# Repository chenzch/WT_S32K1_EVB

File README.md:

MiniEVB for S32K1. Powered by WTMEC.

<Peter_Chen@wtmec.com>

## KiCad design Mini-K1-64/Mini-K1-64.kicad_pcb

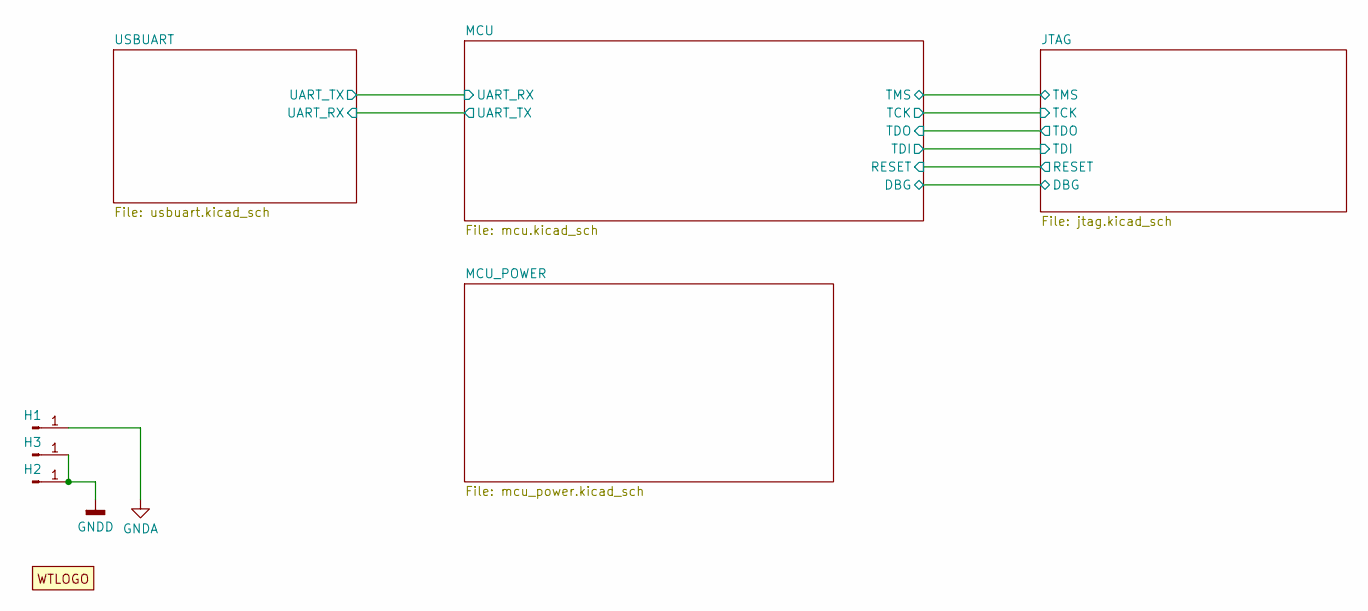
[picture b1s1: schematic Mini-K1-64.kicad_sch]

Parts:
H1, H2, H3: Conn_01x01_Pin; MountingHole_2.2mm_M2_ISO7380_Pad
LOGO1: WTLogo

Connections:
GNDA: H1.1; also elsewhere on the board
GNDD: H2.1, H3.1; also elsewhere on the board

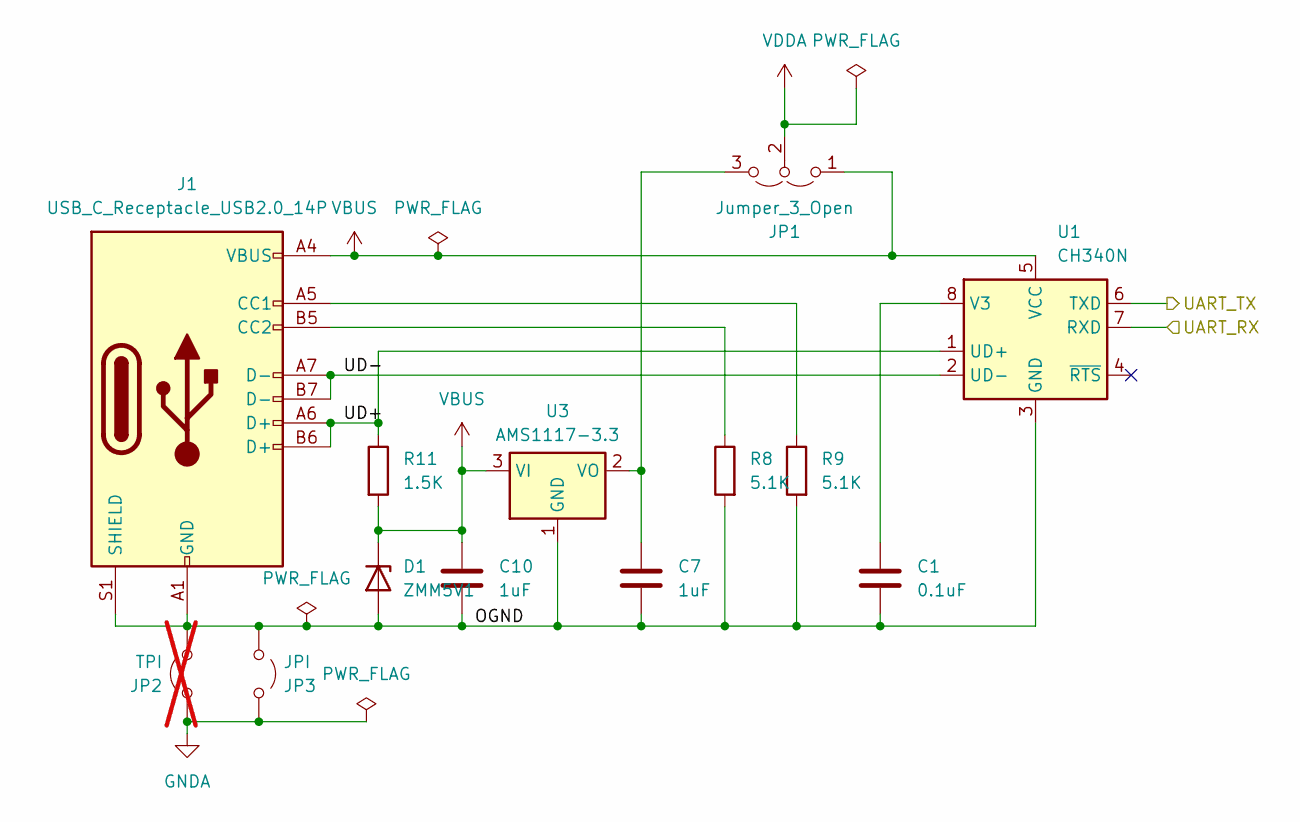
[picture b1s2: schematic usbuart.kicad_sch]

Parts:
C1: 0.1uF; C_0805_2012Metric
C7, C10: 1uF; C_0805_2012Metric
D1: ZMM5V1; D_MiniMELF
J1: USB_C_Receptacle_USB2.0_14P; USB_C_Receptacle_GCT_USB4105-xx-A_16P_TopMnt_Horizontal
JP1: Jumper_3_Open; PinHeader_1x03_P2.54mm_Vertical
JP2: TPI; PinHeader_1x02_P2.54mm_Vertical; not fitted
JP3: JPI; PinHeader_1x02_P2.54mm_Vertical
R8, R9: 5.1K; R_0805_2012Metric
R11: 1.5K; R_0805_2012Metric
U1: CH340N; SOP-8_3.9x4.9mm_P1.27mm
U3: AMS1117-3.3; SOT-223-3_TabPin2

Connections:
/MCU/UART_RX: U1.6 (TXD); also elsewhere on the board
/MCU/UART_TX: U1.7 (RXD); also elsewhere on the board
/USBUART/OGND: C1.2, C7.2, C10.2, D1.2 (A), J1.A1 (GND), J1.A12 (GND), J1.B1 (GND), J1.B12 (GND), J1.S1 (SHIELD), JP2.2 (B), JP3.2 (B), R8.2, R9.2, U1.3 (GND), U3.1 (GND)
/USBUART/UD+: J1.A6 (D+), J1.B6 (D+), R11.1, U1.1 (UD+)
/USBUART/UD-: J1.A7 (D-), J1.B7 (D-), U1.2 (UD-)
GNDA: JP2.1 (A), JP3.1 (A); also elsewhere on the board
unnamed: J1.A5 (CC1), R9.1
unnamed: J1.B5 (CC2), R8.1
unnamed: C7.1, JP1.3 (B), U3.2 (VO)
unnamed: C1.1, U1.8 (V3)
VBUS: C10.1, D1.1 (K), J1.A4 (VBUS), J1.A9 (VBUS), J1.B4 (VBUS), J1.B9 (VBUS), JP1.1 (A), R11.2, U1.5 (VCC), U3.3 (VI)
VDDA: JP1.2 (C); also elsewhere on the board

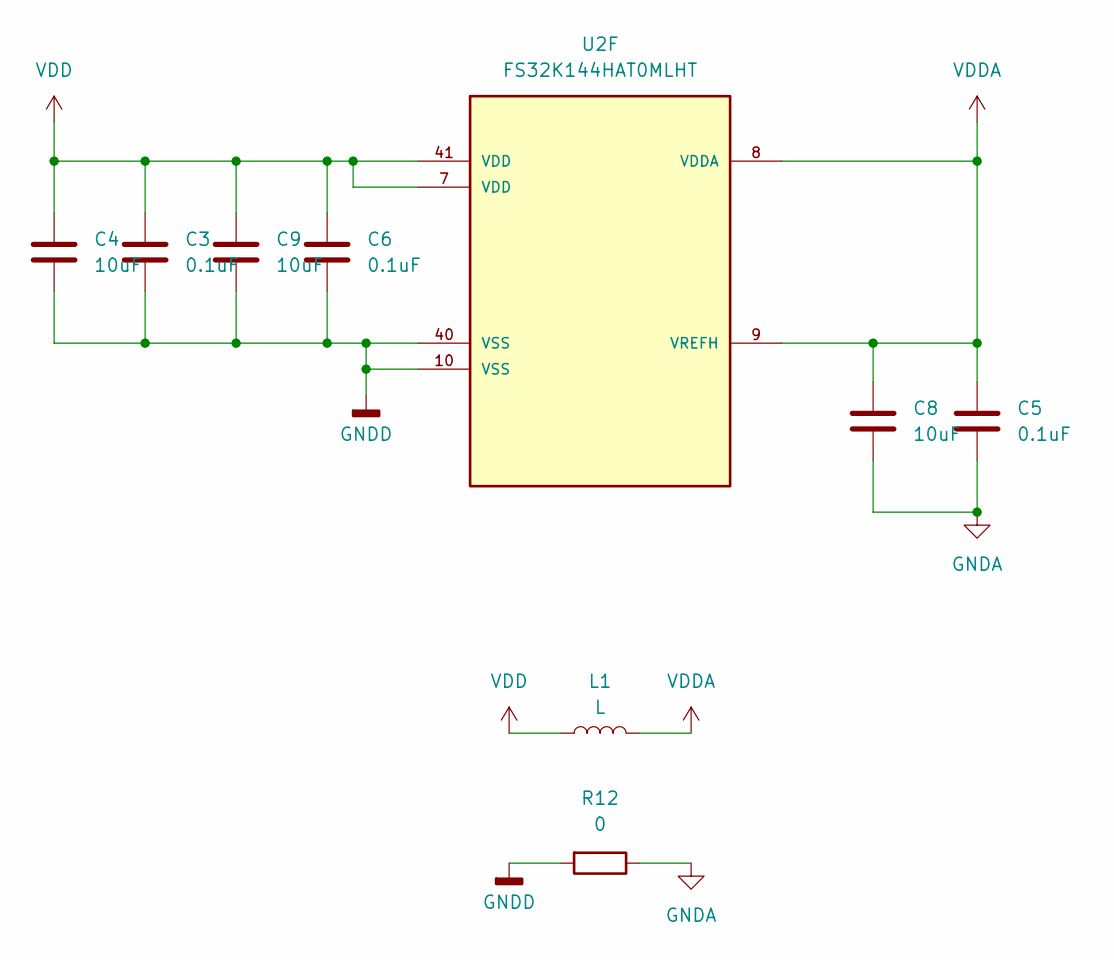
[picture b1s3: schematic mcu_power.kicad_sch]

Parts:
C3, C5, C6: 0.1uF; C_0805_2012Metric
C4, C8, C9: 10uF; C_0805_2012Metric
L1: L; L_0805_2012Metric
R12: 0; R_0805_2012Metric
U2: FS32K144HAT0MLHT; LQFP-64_10x10mm_P0.5mm

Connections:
GNDA: C5.2, C8.2, R12.1; also elsewhere on the board
GNDD: C3.2, C4.2, C6.2, C9.2, R12.2, U2.10 (VSS), U2.40 (VSS); also elsewhere on the board
VDD: C3.1, C4.1, C6.1, C9.1, L1.1, U2.7 (VDD), U2.41 (VDD); also elsewhere on the board
VDDA: C5.1, C8.1, L1.2, U2.8 (VDDA), U2.9 (VREFH); also elsewhere on the board

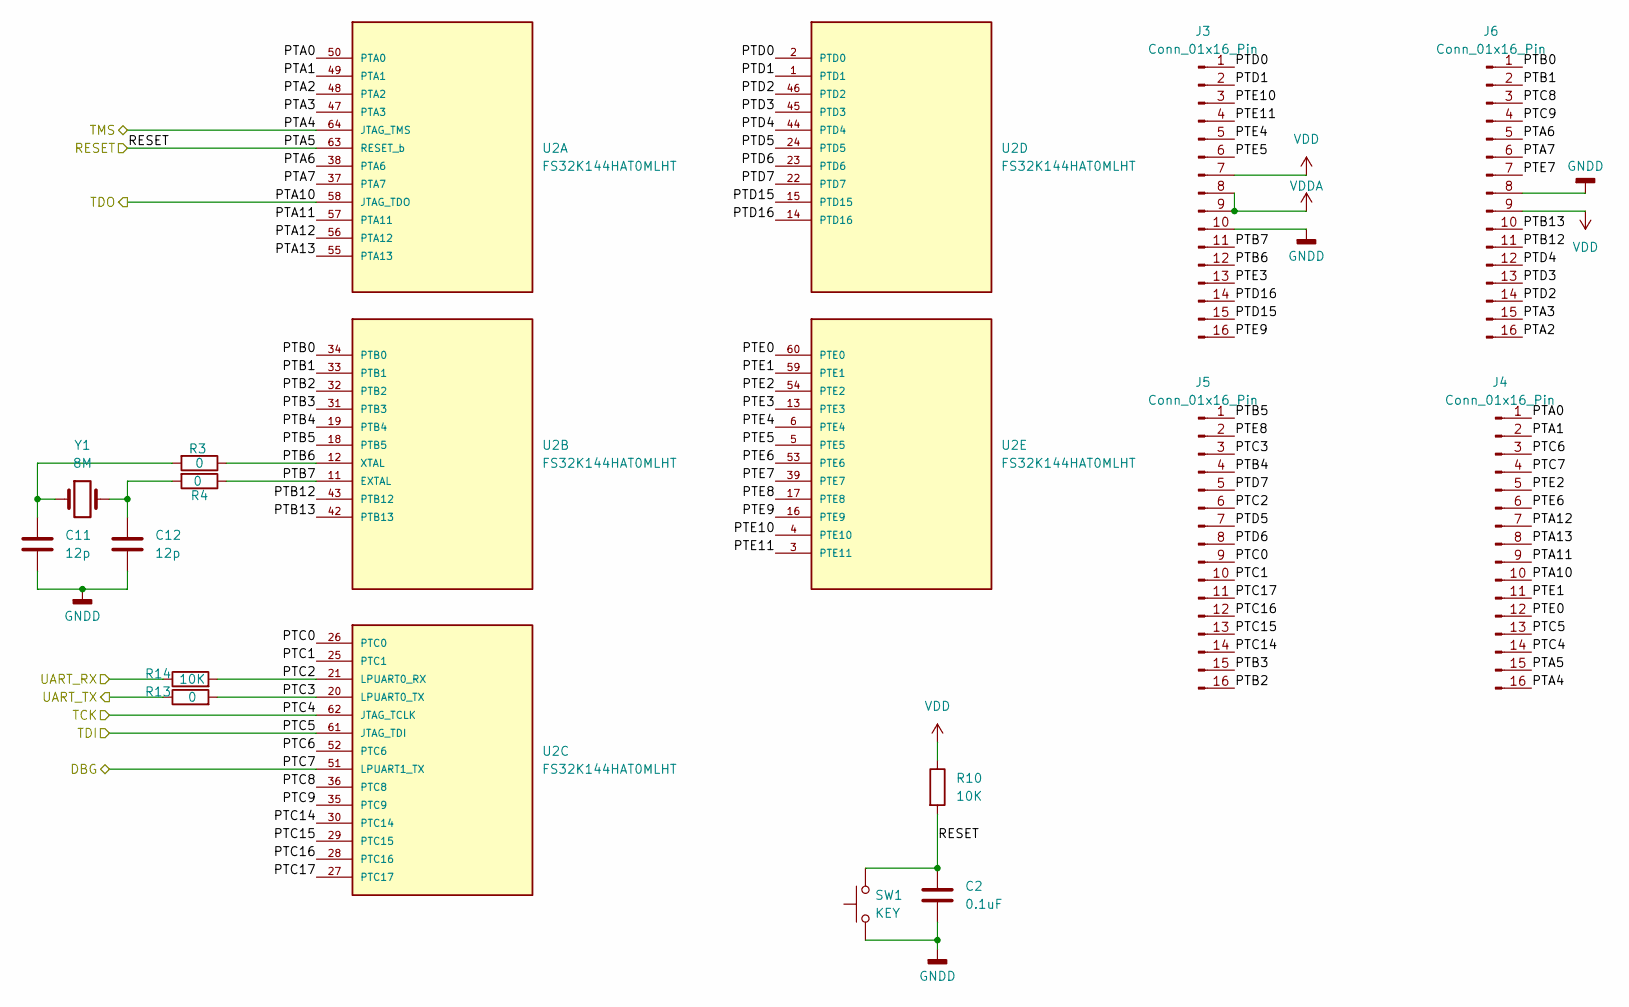
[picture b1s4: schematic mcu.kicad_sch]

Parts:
C2: 0.1uF; C_0805_2012Metric
C11, C12: 12p; C_0805_2012Metric
J3, J4, J5, J6: Conn_01x16_Pin; PinHeader_2x08_P2.54mm_Vertical
R3, R4, R13: 0; R_0805_2012Metric
R10, R14: 10K; R_0805_2012Metric
SW1: KEY; SW_PUSH_6mm_H4.3mm
U2: FS32K144HAT0MLHT; LQFP-64_10x10mm_P0.5mm
Y1: 8M; Crystal_HC49-4H_Vertical

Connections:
/MCU/PTA0: J4.1, U2.50 (PTA0)
/MCU/PTA1: J4.2, U2.49 (PTA1)
/MCU/PTA2: J6.16, U2.48 (PTA2)
/MCU/PTA3: J6.15, U2.47 (PTA3)
/MCU/PTA4: J4.16, U2.64 (JTAG_TMS); also elsewhere on the board
/MCU/PTA5: C2.1, J4.15, R10.2, SW1.2, U2.63 (RESET_b); also elsewhere on the board
/MCU/PTA6: J6.5, U2.38 (PTA6)
/MCU/PTA7: J6.6, U2.37 (PTA7)
/MCU/PTA10: J4.10, U2.58 (JTAG_TDO); also elsewhere on the board
/MCU/PTA11: J4.9, U2.57 (PTA11)
/MCU/PTA12: J4.7, U2.56 (PTA12)
/MCU/PTA13: J4.8, U2.55 (PTA13)
/MCU/PTB0: J6.1, U2.34 (PTB0)
/MCU/PTB1: J6.2, U2.33 (PTB1)
/MCU/PTB2: J5.16, U2.32 (PTB2)
/MCU/PTB3: J5.15, U2.31 (PTB3)
/MCU/PTB4: J5.4, U2.19 (PTB4)
/MCU/PTB5: J5.1, U2.18 (PTB5)
/MCU/PTB6: J3.12, R3.1, U2.12 (XTAL)
/MCU/PTB7: J3.11, R4.1, U2.11 (EXTAL)
/MCU/PTB12: J6.11, U2.43 (PTB12)
/MCU/PTB13: J6.10, U2.42 (PTB13)
/MCU/PTC0: J5.9, U2.26 (PTC0)
/MCU/PTC1: J5.10, U2.25 (PTC1)
/MCU/PTC2: J5.6, R14.2, U2.21 (LPUART0_RX)
/MCU/PTC3: J5.3, R13.2, U2.20 (LPUART0_TX)
/MCU/PTC4: J4.14, U2.62 (JTAG_TCLK); also elsewhere on the board
/MCU/PTC5: J4.13, U2.61 (JTAG_TDI); also elsewhere on the board
/MCU/PTC6: J4.3, U2.52 (PTC6)
/MCU/PTC7: J4.4, U2.51 (LPUART1_TX); also elsewhere on the board
/MCU/PTC8: J6.3, U2.36 (PTC8)
/MCU/PTC9: J6.4, U2.35 (PTC9)
/MCU/PTC14: J5.14, U2.30 (PTC14)
/MCU/PTC15: J5.13, U2.29 (PTC15)
/MCU/PTC16: J5.12, U2.28 (PTC16)
/MCU/PTC17: J5.11, U2.27 (PTC17)
/MCU/PTD0: J3.1, U2.2 (PTD0)
/MCU/PTD1: J3.2, U2.1 (PTD1)
/MCU/PTD2: J6.14, U2.46 (PTD2)
/MCU/PTD3: J6.13, U2.45 (PTD3)
/MCU/PTD4: J6.12, U2.44 (PTD4)
/MCU/PTD5: J5.7, U2.24 (PTD5)
/MCU/PTD6: J5.8, U2.23 (PTD6)
/MCU/PTD7: J5.5, U2.22 (PTD7)
/MCU/PTD15: J3.15, U2.15 (PTD15)
/MCU/PTD16: J3.14, U2.14 (PTD16)
/MCU/PTE0: J4.12, U2.60 (PTE0)
/MCU/PTE1: J4.11, U2.59 (PTE1)
/MCU/PTE2: J4.5, U2.54 (PTE2)
/MCU/PTE3: J3.13, U2.13 (PTE3)
/MCU/PTE4: J3.5, U2.6 (PTE4)
/MCU/PTE5: J3.6, U2.5 (PTE5)
/MCU/PTE6: J4.6, U2.53 (PTE6)
/MCU/PTE7: J6.7, U2.39 (PTE7)
/MCU/PTE8: J5.2, U2.17 (PTE8)
/MCU/PTE9: J3.16, U2.16 (PTE9)
/MCU/PTE10: J3.3, U2.4 (PTE10)
/MCU/PTE11: J3.4, U2.3 (PTE11)
/MCU/UART_RX: R14.1; also elsewhere on the board
/MCU/UART_TX: R13.1; also elsewhere on the board
GNDD: C2.2, C11.2, C12.2, J3.10, J6.8, SW1.1; also elsewhere on the board
unnamed: C11.1, R3.2, Y1.1
unnamed: C12.1, R4.2, Y1.2
VDD: J3.7, J6.9, R10.1; also elsewhere on the board
VDDA: J3.8, J3.9; also elsewhere on the board

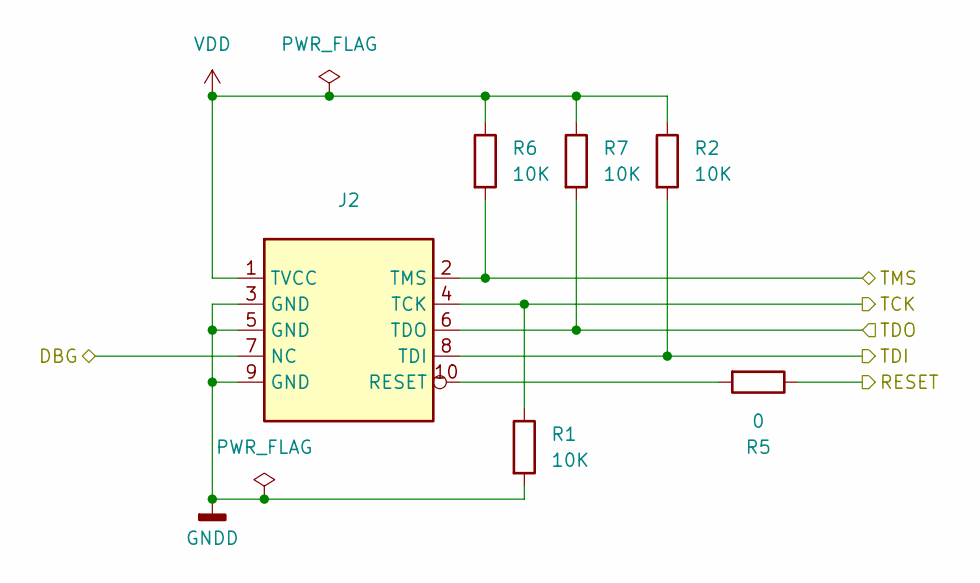
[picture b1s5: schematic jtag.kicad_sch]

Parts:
J2: PinHeader_2x05_P1.27mm_Vertical
R1, R2, R6, R7: 10K; R_0805_2012Metric
R5: 0; R_0805_2012Metric

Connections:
/MCU/PTA4: J2.2 (TMS), R6.2; also elsewhere on the board
/MCU/PTA5: R5.1; also elsewhere on the board
/MCU/PTA10: J2.6 (TDO), R7.2; also elsewhere on the board
/MCU/PTC4: J2.4 (TCK), R1.1; also elsewhere on the board
/MCU/PTC5: J2.8 (TDI), R2.2; also elsewhere on the board
/MCU/PTC7: J2.7 (NC); also elsewhere on the board
GNDD: J2.3 (GND), J2.5 (GND), J2.9 (GND), R1.2; also elsewhere on the board
unnamed: J2.10 (RESET), R5.2
VDD: J2.1 (TVCC), R2.1, R6.1, R7.1; also elsewhere on the board

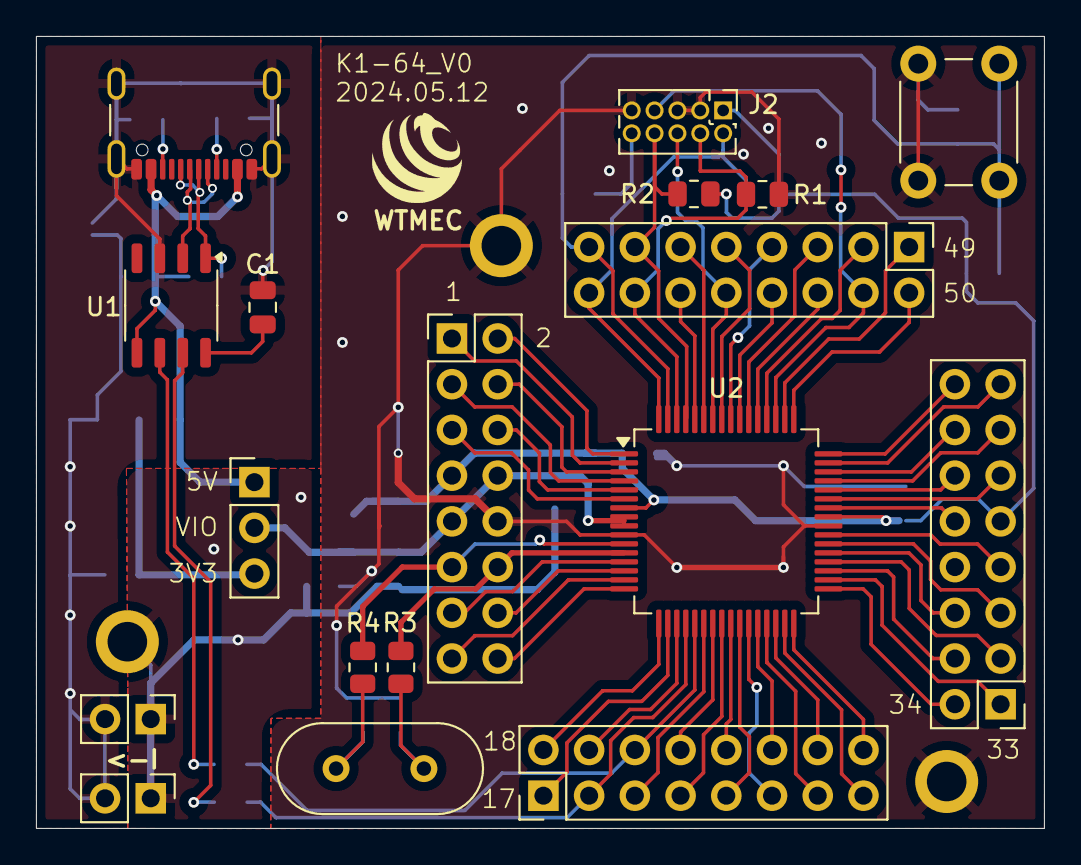
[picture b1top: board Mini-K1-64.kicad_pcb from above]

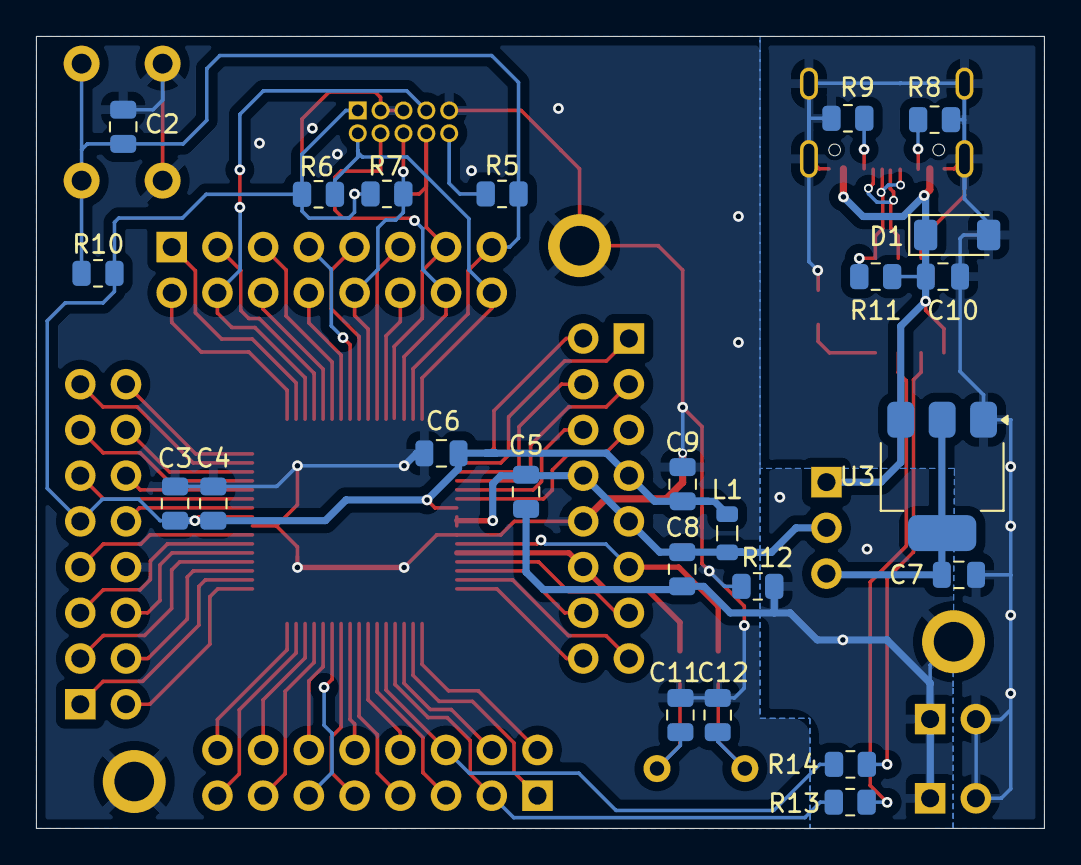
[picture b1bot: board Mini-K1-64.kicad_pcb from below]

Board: 2 copper layers, 56.0 x 44.0 mm, 46 parts (24 on the bottom side), 75 nets.

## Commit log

2024-05-07 Add Mini-K1-64
2024-05-07 Add README
2024-05-07 Fix via position
2024-05-08 Format PCB
2024-05-09 Add Symbol
2024-05-11 Step Update
2024-05-12 Rev0
2024-05-13 Update Gerber
2024-06-06 Update Lines
2024-06-30 Update Debug Connector
2025-03-02 Update to Kicad 9
